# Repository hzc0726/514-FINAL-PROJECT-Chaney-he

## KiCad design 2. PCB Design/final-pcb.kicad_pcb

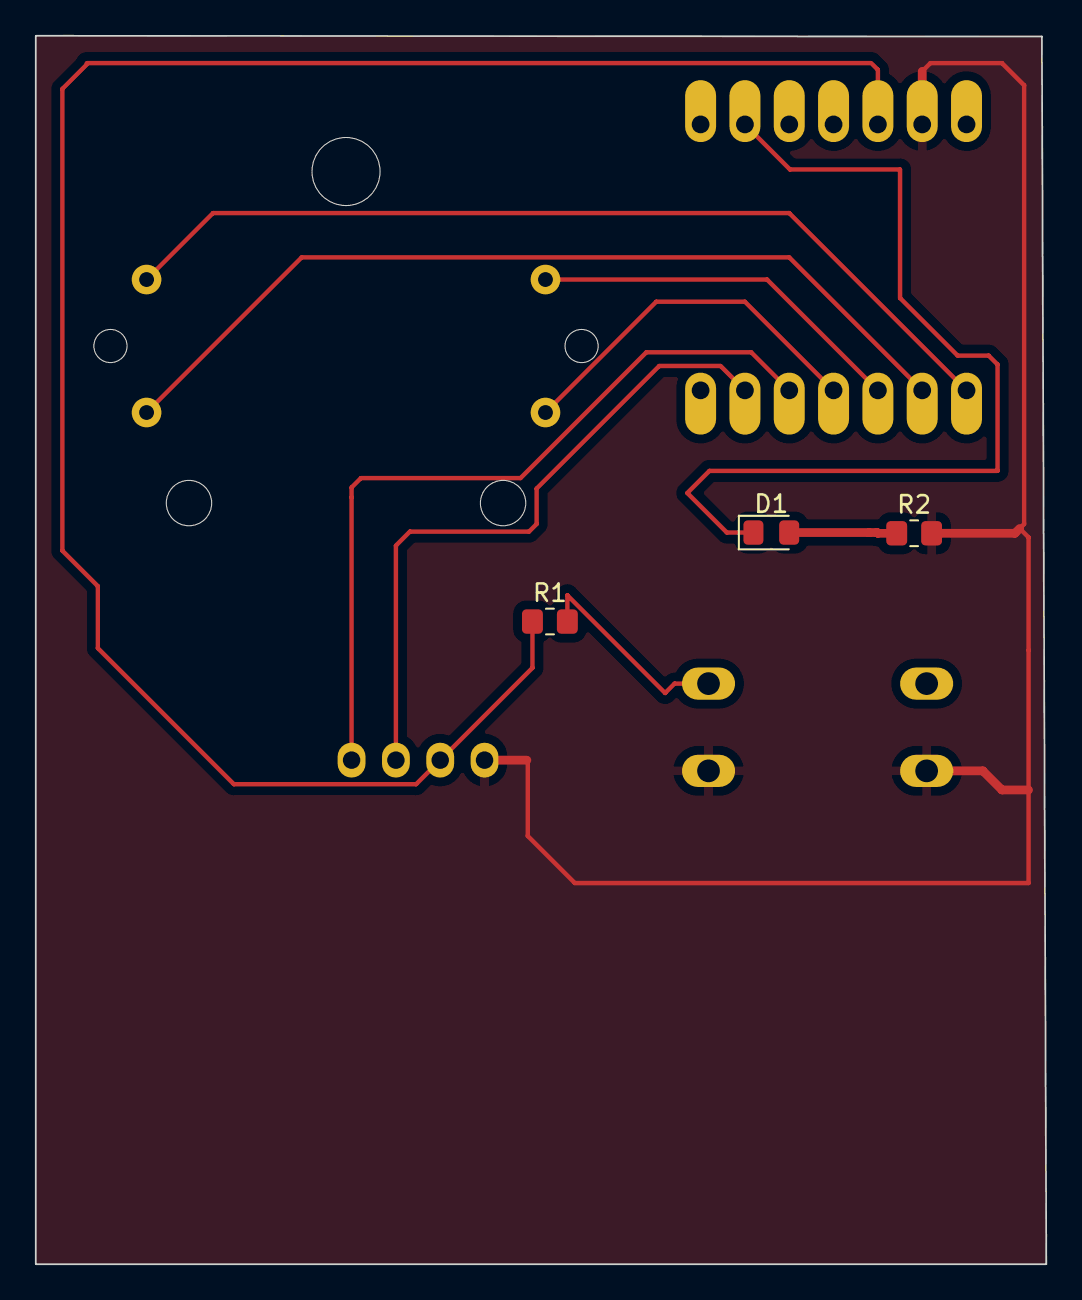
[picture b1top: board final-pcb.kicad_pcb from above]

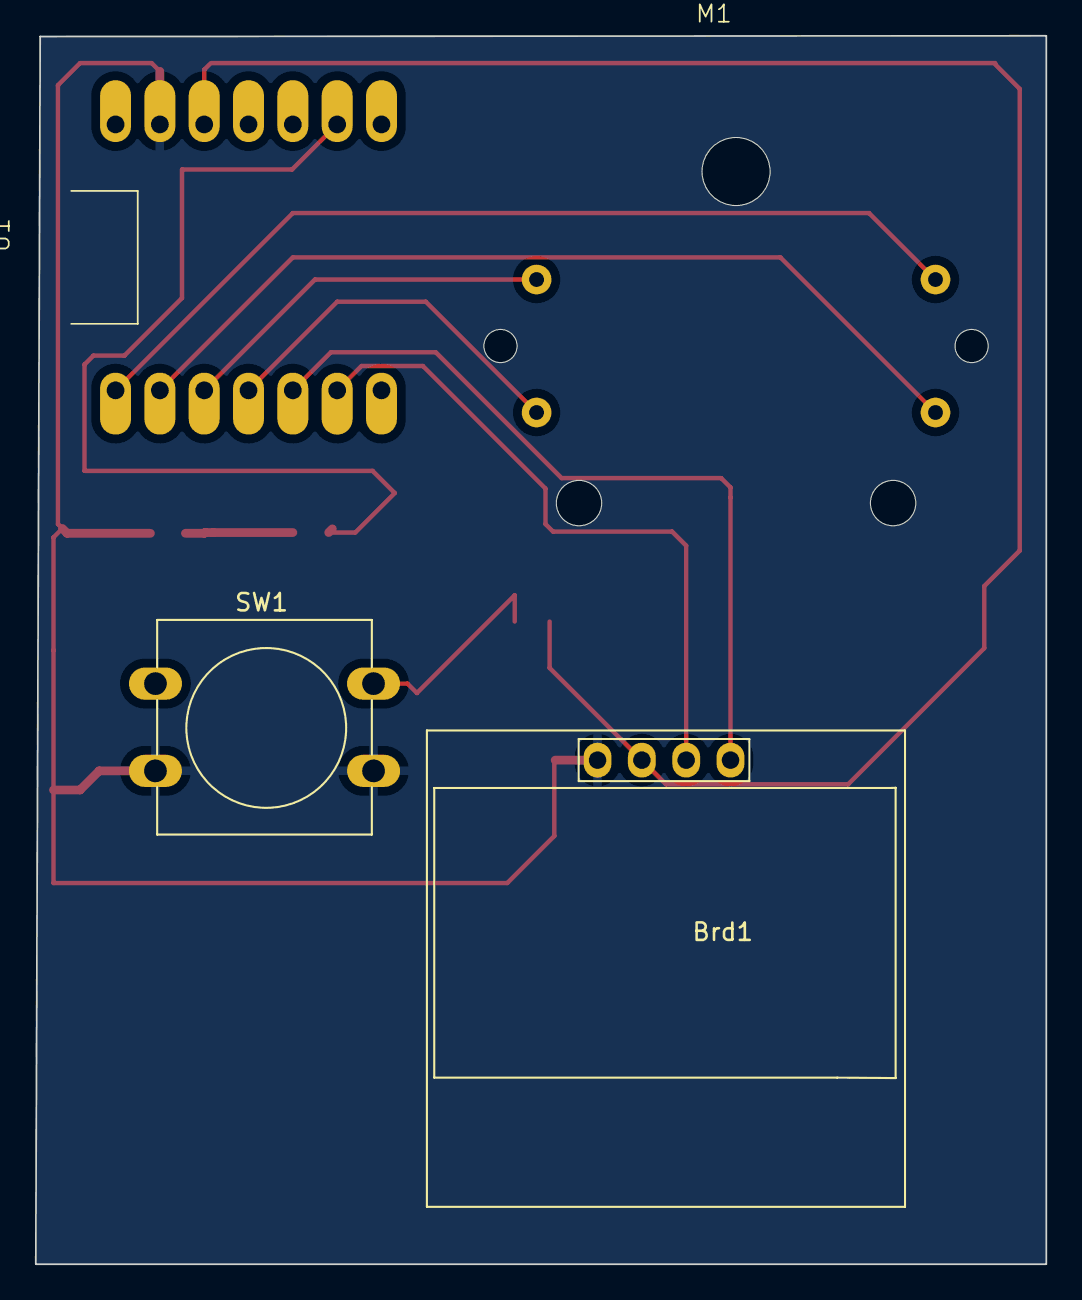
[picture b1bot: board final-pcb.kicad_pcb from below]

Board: 2 copper layers, 57.9 x 70.4 mm, 7 parts (4 on the bottom side), 11 nets.

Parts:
Brd1: SSD1306; 128x64OLED
D1: LED; LED_0805_2012Metric_Pad1.15x1.40mm_HandSolder
M1: Stepper_Motor_bipolar; x27_stepper_two_holes
R1: 13 ohms; R_0805_2012Metric_Pad1.20x1.40mm_HandSolder
R2: 165 ohm; R_0805_2012Metric_Pad1.20x1.40mm_HandSolder
SW1: SW_SPST; SW_PUSH-12mm
U1: XIAO_ESP32_SENSE

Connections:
GND: Brd1.1 (GND), R2.2, SW1.2 (B), U1.9 (GND)
unnamed: Brd1.3 (SCL), U1.6 (GPIO6_A5_D5_SCL)
unnamed: Brd1.4 (SDA), U1.5 (GPIO4_A3_D3_SDA)
unnamed: Brd1.2 (VCC), R1.1, U1.10 (3V3)
unnamed: D1.2 (A), R2.1
unnamed: M1.2 (-), U1.2 (GPIO2_A1_D1)
unnamed: R1.2, SW1.1 (A)
unnamed: M1.1, U1.1 (GPIO1_A0_D0)
unnamed: M1.3, U1.3 (GPIO3_A2_D2)
unnamed: M1.4, U1.4 (GPIO4_A3_D3)
unnamed: D1.1 (K), U1.13 (GPIO7_A8_D8_SCK)

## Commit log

2024-02-20 FINAL
